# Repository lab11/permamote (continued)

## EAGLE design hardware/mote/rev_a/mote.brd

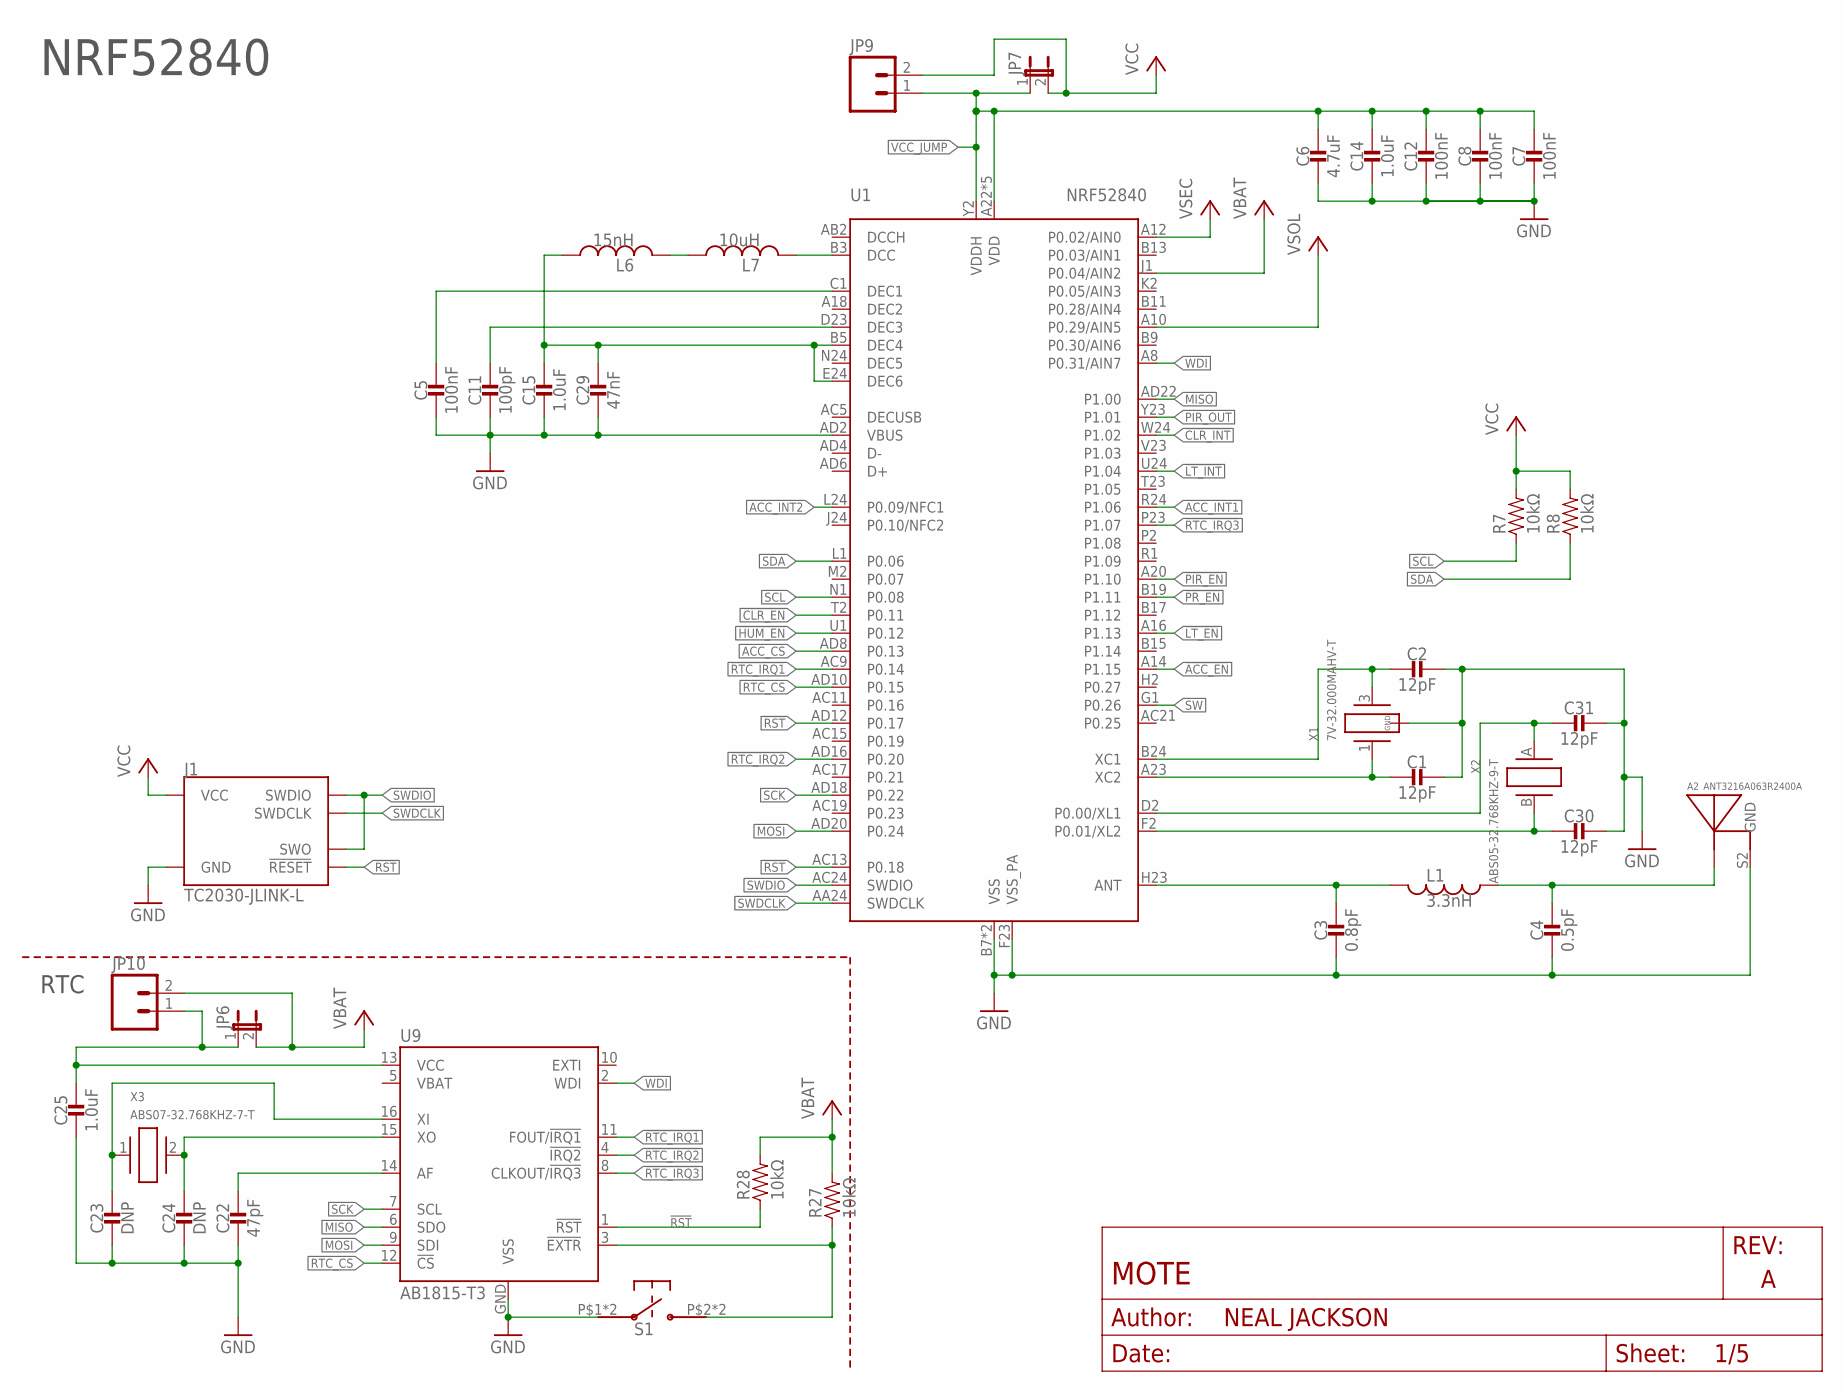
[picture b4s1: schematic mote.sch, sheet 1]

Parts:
A2: ANT3216A063R2400A
C1, C2, C30, C31: 12pF; 0402_CAP; DIGIKEY 490-6197-1-ND
C3: 0.8pF; 0402_CAP; DIGIKEY 490-6269-1-ND
C4: 0.5pF; 0402_CAP; DIGIKEY 490-6264-1-ND
C5, C7, C8, C12: 100nF; 0402_CAP; DIGIKEY 490-6328-1-ND
C6: 4.7uF; 0603_CAP; DIGIKEY 445-5947-1-ND
C11: 100pF; 0402_CAP; DIGIKEY 490-5922-1-ND
C14, C15, C25: 1.0uF; 0402_CAP; DIGIKEY 490-7195-1-ND
C22: 47pF; 0402_CAP; DIGIKEY 490-5942-1-ND
C23, C24: DNP; 0402_CAP
C29: 47nF; 0402_CAP; DIGIKEY 445-1264-1-ND
J1: TC2030-JLINK-L; TC2030-IDC
JP6, JP7: JUMPER-2SMD-NC; SJ_2S
JP9, JP10: M02PTH; 1X02
L1: 3.3nH; 0402_CAP; DIGIKEY 535-10426-1-ND
L6: 15nH; 0402_CAP; DIGIKEY 587-1521-1-ND
L7: 10uH; 0603_CAP; DIGIKEY 490-4025-1-ND
R7, R8, R27, R28: 10kΩ; 0402_RES; DIGIKEY 311-10KJRCT-ND
S1: EVQP2
U1: NRF52840; AQFN73
U9: AB1815-T3; QFN-16-3MM
X1: 7V-32.000MAHV-T; TXC-7V
X2: ABS05-32.768KHZ-9-T; ABS05
X3: ABS07-32.768KHZ-7-T; 2-SMD

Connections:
!ACC_EN: U1.A14 (P1.15); also elsewhere on the board
!CLR_EN: U1.T2 (P0.11); also elsewhere on the board
!CLR_INT: U1.W24 (P1.02); also elsewhere on the board
!HUM_EN: U1.U1 (P0.12); also elsewhere on the board
!LT_EN: U1.A16 (P1.13); also elsewhere on the board
!LT_INT: U1.U24 (P1.04); also elsewhere on the board
!PIR_EN: U1.A20 (P1.10); also elsewhere on the board
!PR_EN: U1.B19 (P1.11); also elsewhere on the board
!RST: J1.3 (!RESET), R28.1, U1.AC13 (P0.18), U1.AD12 (P0.17), U9.1 (!RST); also elsewhere on the board
!RTC_EXTR: R27.1, S1.P$2, S1.P$4, U9.3 (!EXTR)
!RTC_IRQ1: U1.AC9 (P0.14), U9.11 (FOUT/!IRQ1); also elsewhere on the board
!RTC_IRQ2: U1.AD16 (P0.20), U9.4 (!IRQ2); also elsewhere on the board
!RTC_IRQ3: U1.P23 (P1.07), U9.8 (CLKOUT/!IRQ3); also elsewhere on the board
ACC_CS: U1.AD8 (P0.13); also elsewhere on the board
ACC_INT1: U1.R24 (P1.06); also elsewhere on the board
ACC_INT2: U1.L24 (P0.09/NFC1); also elsewhere on the board
GND: A2.S2 (GND), C1.1, C2.1, C3.2, C4.2, C5.2, C6.2, C7.2, C8.2, C11.2, C12.2, C14.2, C15.2, C22.2, C23.2, C24.2, C25.2, C29.2, C30.1, C31.1, J1.5 (GND), S1.P$1, S1.P$3, U1.AD2 (VBUS), U1.B7 (VSS), U1.F23 (VSS_PA), U1.GND (VSS), U9.GND (VSS), X1.2 (GND), X1.4 (GND); also elsewhere on the board
MISO: U1.AD22 (P1.00), U9.6 (SDO); also elsewhere on the board
MOSI: U1.AD20 (P0.24), U9.9 (SDI); also elsewhere on the board
unnamed: C5.1, U1.C1 (DEC1)
unnamed: C15.1, C29.1, L6.1, U1.B5 (DEC4), U1.E24 (DEC6)
unnamed: C11.1, U1.D23 (DEC3)
unnamed: C3.1, L1.2, U1.H23 (ANT)
unnamed: A2.S1 (ANTENNA), C4.1, L1.1
unnamed: C2.2, U1.B24 (XC1), X1.3 (2)
unnamed: C1.2, U1.A23 (XC2), X1.1
unnamed: C22.1, U9.14 (AF)
unnamed: C23.1, U9.16 (XI), X3.1
unnamed: C24.1, U9.15 (XO), X3.2
unnamed: C25.1, JP6.1, JP10.1, U9.13 (VCC)
unnamed: L7.2, U1.B3 (DCC)
unnamed: L6.2, L7.1
PIR_OUT: U1.Y23 (P1.01); also elsewhere on the board
RTC_CS: U1.AD10 (P0.15), U9.12 (!CS); also elsewhere on the board
SCK: U1.AD18 (P0.22), U9.7 (SCL); also elsewhere on the board
SCL: R7.1, U1.N1 (P0.08); also elsewhere on the board
SDA: R8.1, U1.L1 (P0.06); also elsewhere on the board
SW: U1.G1 (P0.26); also elsewhere on the board
SWDCLK: J1.4 (SWDCLK), U1.AA24 (SWDCLK); also elsewhere on the board
SWDIO: J1.2 (SWDIO), J1.6 (SWO), U1.AC24 (SWDIO); also elsewhere on the board
VBAT: JP6.2, JP10.2, R27.2, R28.2, U1.J1 (P0.04/AIN2); also elsewhere on the board
VCC: J1.1 (VCC), JP7.2, JP9.2, R7.2, R8.2; also elsewhere on the board
VCC_JUMP: C6.1, C7.1, C8.1, C12.1, C14.1, JP7.1, JP9.1, U1.A22 (VDD), U1.AD14 (VDD), U1.AD23 (VDD), U1.B1 (VDD), U1.W1 (VDD), U1.Y2 (VDDH); also elsewhere on the board
VSEC: U1.A12 (P0.02/AIN0); also elsewhere on the board
VSOL: U1.A10 (P0.29/AIN5); also elsewhere on the board
WDI: U1.A8 (P0.31/AIN7), U9.2 (WDI); also elsewhere on the board
XL1: C31.2, U1.D2 (P0.00/XL1), X2.A (1)
XL2: C30.2, U1.F2 (P0.01/XL2), X2.B (2)

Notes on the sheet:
NRF52840
RTC

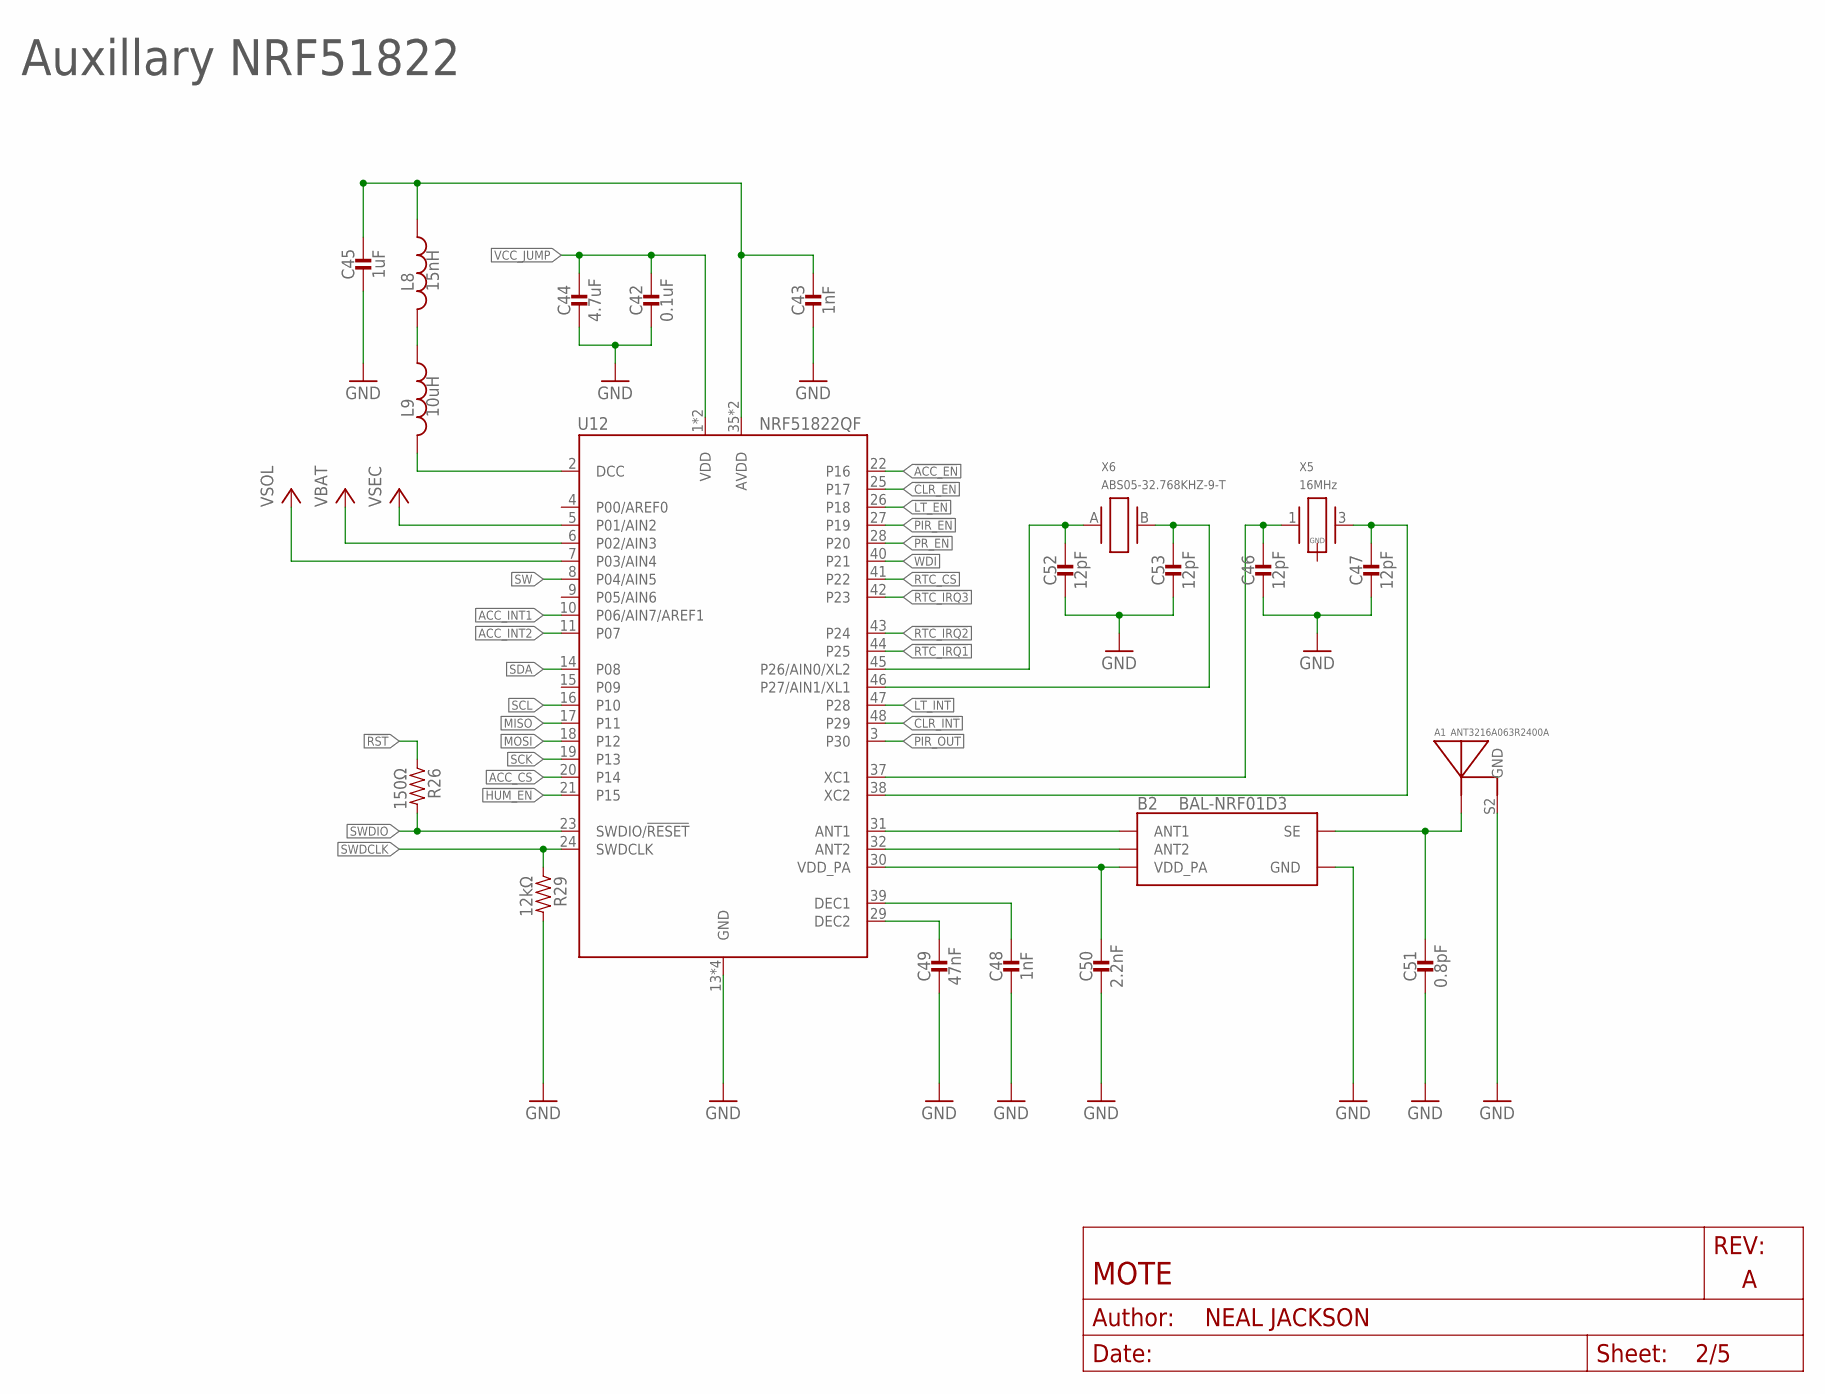
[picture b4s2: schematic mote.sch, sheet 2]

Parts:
A1: ANT3216A063R2400A
B2: BAL-NRF01D3
C42: 0.1uF; 0402_CAP; DIGIKEY 490-6328-1-ND
C43, C48: 1nF; 0402_CAP; DIGIKEY 490-1303-1-ND
C44: 4.7uF; 0402_CAP; DIGIKEY 445-5947-1-ND
C45: 1uF; 0402_CAP; DIGIKEY 1276-1513-1-ND
C46, C47, C52, C53: 12pF; 0402_CAP; DIGIKEY 490-6197-1-ND
C49: 47nF; 0402_CAP; DIGIKEY 445-1264-1-ND
C50: 2.2nF; 0402_CAP; DIGIKEY 490-5419-1-ND
C51: 0.8pF; 0402_CAP; DIGIKEY 490-6269-1-ND
L8: 15nH; 0402_CAP; DIGIKEY 587-1521-1-ND
L9: 10uH; 0603_CAP; DIGIKEY 490-4025-1-ND
R26: 150Ω; 0402_RES; DIGIKEY RHM12.0KCDCT-ND
R29: 12kΩ; 0402_RES; DIGIKEY RHM12.0KCDCT-ND
U12: NRF51822QF; QFN-48-6MM
X5: 16MHz; TXC-8Y; DIGIKEY 887-2003-1-ND
X6: ABS05-32.768KHZ-9-T; ABS05

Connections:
!ACC_EN: U12.22 (P16); also elsewhere on the board
!CLR_EN: U12.25 (P17); also elsewhere on the board
!CLR_INT: U12.48 (P29); also elsewhere on the board
!HUM_EN: U12.21 (P15); also elsewhere on the board
!LT_EN: U12.26 (P18); also elsewhere on the board
!LT_INT: U12.47 (P28); also elsewhere on the board
!PIR_EN: U12.27 (P19); also elsewhere on the board
!PR_EN: U12.28 (P20); also elsewhere on the board
!RST: R26.1; also elsewhere on the board
!RTC_IRQ1: U12.44 (P25); also elsewhere on the board
!RTC_IRQ2: U12.43 (P24); also elsewhere on the board
!RTC_IRQ3: U12.42 (P23); also elsewhere on the board
ACC_CS: U12.20 (P14); also elsewhere on the board
ACC_INT1: U12.10 (P06/AIN7/AREF1); also elsewhere on the board
ACC_INT2: U12.11 (P07); also elsewhere on the board
AVDD1: C43.1, C45.1, L8.1, U12.35 (AVDD), U12.36 (AVDD)
DCC1: L9.2, U12.2 (DCC)
GND: A1.S2 (GND), B2.GND, C42.2, C43.2, C44.2, C45.2, C46.2, C47.2, C48.2, C49.2, C50.2, C51.2, C52.2, C53.2, R29.2, U12.13 (GND), U12.33 (GND), U12.34 (GND), U12.GND; also elsewhere on the board
MISO: U12.17 (P11); also elsewhere on the board
MOSI: U12.18 (P12); also elsewhere on the board
unnamed: B2.ANT1, U12.31 (ANT1)
unnamed: B2.ANT2, U12.32 (ANT2)
unnamed: A1.S1 (ANTENNA), B2.SE, C51.1
unnamed: L8.2, L9.1
unnamed: C46.1, U12.37 (XC1), X5.1
unnamed: C47.1, U12.38 (XC2), X5.3 (2)
unnamed: C48.1, U12.39 (DEC1)
unnamed: C49.1, U12.29 (DEC2)
NRF_A2: C53.1, U12.46 (P27/AIN1/XL1), X6.B (2)
NRF_A3: C52.1, U12.45 (P26/AIN0/XL2), X6.A (1)
PIR_OUT: U12.3 (P30); also elsewhere on the board
RTC_CS: U12.41 (P22); also elsewhere on the board
SCK: U12.19 (P13); also elsewhere on the board
SCL: U12.16 (P10); also elsewhere on the board
SDA: U12.14 (P08); also elsewhere on the board
SW: U12.8 (P04/AIN5); also elsewhere on the board
SWDCLK: R29.1, U12.24 (SWDCLK); also elsewhere on the board
SWDIO: R26.2, U12.23 (SWDIO/!RESET); also elsewhere on the board
VBAT: U12.6 (P02/AIN3); also elsewhere on the board
VCC_JUMP: C42.1, C44.1, U12.1 (VDD), U12.12 (VDD); also elsewhere on the board
VDD_PA1: B2.VCC (VDD_PA), C50.1, U12.30 (VDD_PA)
VSEC: U12.5 (P01/AIN2); also elsewhere on the board
VSOL: U12.7 (P03/AIN4); also elsewhere on the board
WDI: U12.40 (P21); also elsewhere on the board

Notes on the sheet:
Auxillary NRF51822

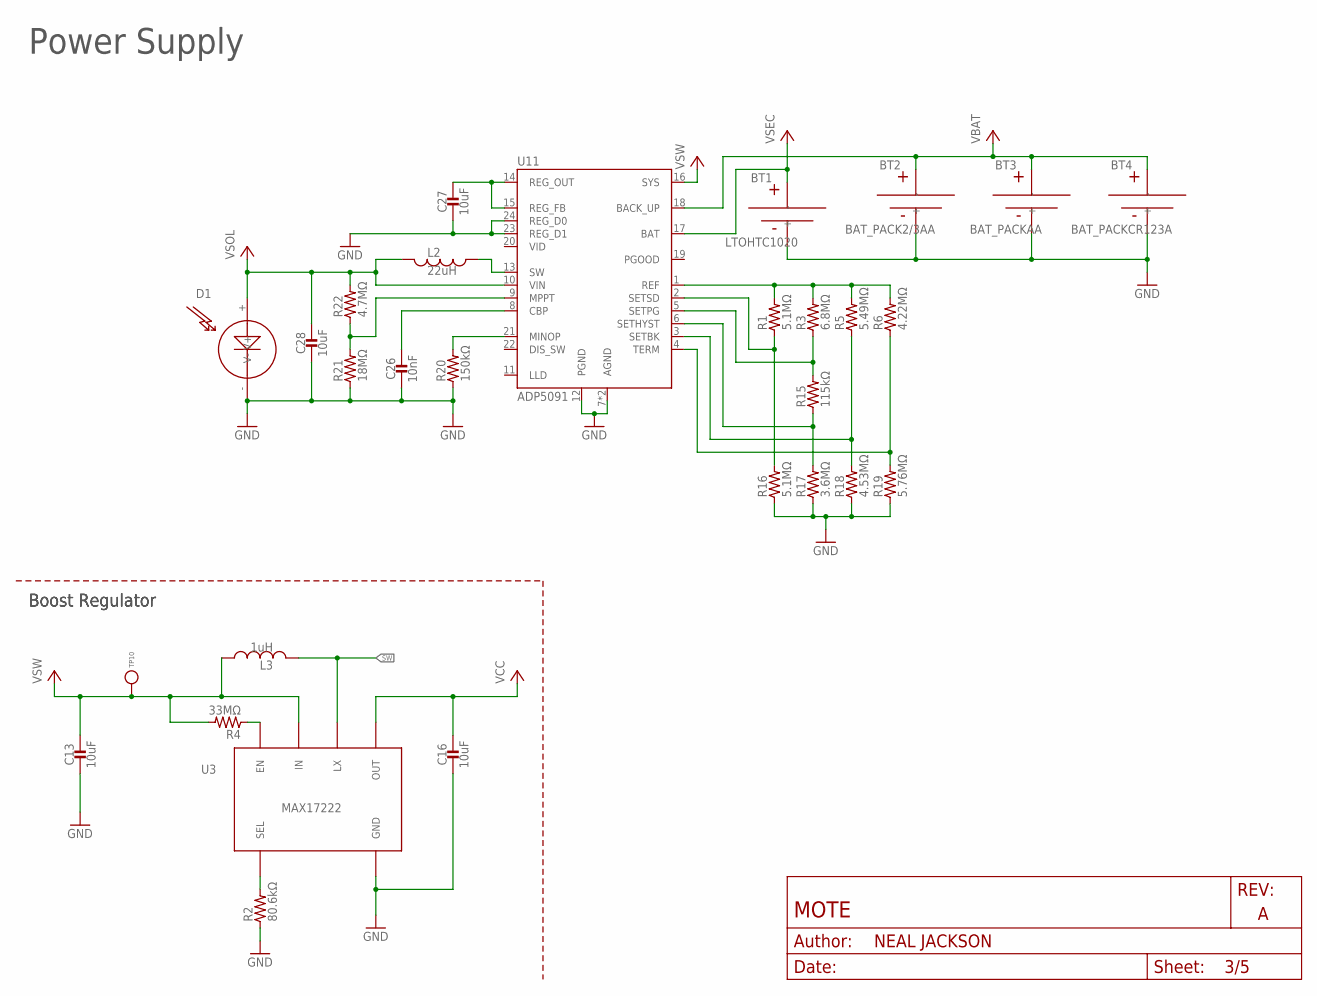
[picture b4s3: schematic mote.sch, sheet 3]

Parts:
BT1: LTOHTC1020; 1020
BT2: BAT_PACK2/3AA; 6S-2-3A
BT3: BAT_PACKAA; BHAA-3
BT4: BAT_PACKCR123A; BH123A
C13, C16, C27, C28: 10uF; 0603_CAP; DIGIKEY 490-3896-2-ND
C26: 10nF; 0603_CAP; DIGIKEY 490-4516-1-ND
D1: SOLARCELL; SOLAR_HOLES
L2: 22uH; 74437324220; DIGIKEY 732-3340-1-ND
L3: 1uH; IHL-2525CZ; DIGIKEY 541-2562-1-ND
R1, R16: 5.1MΩ; 0402_RES; DIGIKEY YAG3306CT-ND
R2: 80.6kΩ; 0603-RES; DIGIKEY 311-80.6KHRCT-ND
R3: 6.8MΩ; 0402_RES; DIGIKEY YAG3310CT-ND
R4: 33MΩ; 0603-RES; DIGIKEY HMC0603JT33M0CT-ND
R5: 5.49MΩ; 0603-RES; DIGIKEY 541-5.49MHCT-ND
R6: 4.22MΩ; 0402_RES; DIGIKEY 541-4.22MLCT-ND
R15: 115kΩ; 0402_RES; DIGIKEY YAG2956CT-ND
R17: 3.6MΩ; 0402_RES; DIGIKEY 311-3.60MLRCT-ND
R18: 4.53MΩ; 0402_RES; DIGIKEY 541-4.53MLCT-ND
R19: 5.76MΩ; 0805_RES; DIGIKEY 311-5.76MCRCT-ND
R20: 150kΩ; 0402_RES; DIGIKEY 311-1.00MLRCT-ND
R21: 18MΩ; 0603-RES; DIGIKEY P18MGCT-ND
R22: 4.7MΩ; 0402_RES; DIGIKEY YAG3304CT-ND
TP10: TEST_POINT_0.040IN; TESTPOINT_0.040IN
U3: MAX17222; UDFN-6-MAXIM
U11: ADP5091; QFN-24-4MM

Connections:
GND: BT1.-, BT2.-, BT3.-, BT4.-, C13.2, C16.2, C26.2, C27.2, C28.2, D1.- (V-), R2.1, R16.1, R17.1, R18.1, R19.1, R20.1, R21.1, U3.3 (GND), U11.7 (AGND), U11.12 (PGND), U11.23 (REG_D1), U11.24 (REG_D0), U11.GND_PAD (AGND); also elsewhere on the board
unnamed: R1.1, R16.2, U11.2 (SETSD)
unnamed: R1.2, R3.2, R5.2, R6.2, U11.1 (REF)
unnamed: R3.1, R15.2, U11.5 (SETPG)
unnamed: R2.2, U3.4 (SEL)
unnamed: R15.1, R17.2, U11.6 (SETHYST)
unnamed: R4.1, U3.6 (EN)
unnamed: R5.1, R18.2, U11.3 (SETBK)
unnamed: R6.1, R19.2, U11.4 (TERM)
unnamed: R20.2, U11.21 (MINOP)
unnamed: C26.1, U11.8 (CBP)
unnamed: R21.2, R22.1, U11.9 (MPPT)
unnamed: L2.P$1 (1), U11.13 (SW)
unnamed: C27.1, U11.14 (REG_OUT), U11.15 (REG_FB)
SW: L3.P$2 (2), U3.2 (LX); also elsewhere on the board
VBAT: BT2.+, BT3.+, BT4.+, U11.18 (BACK_UP); also elsewhere on the board
VCC: C16.1, U3.1 (OUT); also elsewhere on the board
VSEC: BT1.+, U11.17 (BAT); also elsewhere on the board
VSOL: C28.1, D1.+ (V+), L2.P$2 (2), R22.2, U11.10 (VIN); also elsewhere on the board
VSW: C13.1, L3.P$1 (1), R4.2, TP10.TESTPOINT, U3.5 (IN), U11.16 (SYS)

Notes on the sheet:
Power Supply
Boost Regulator

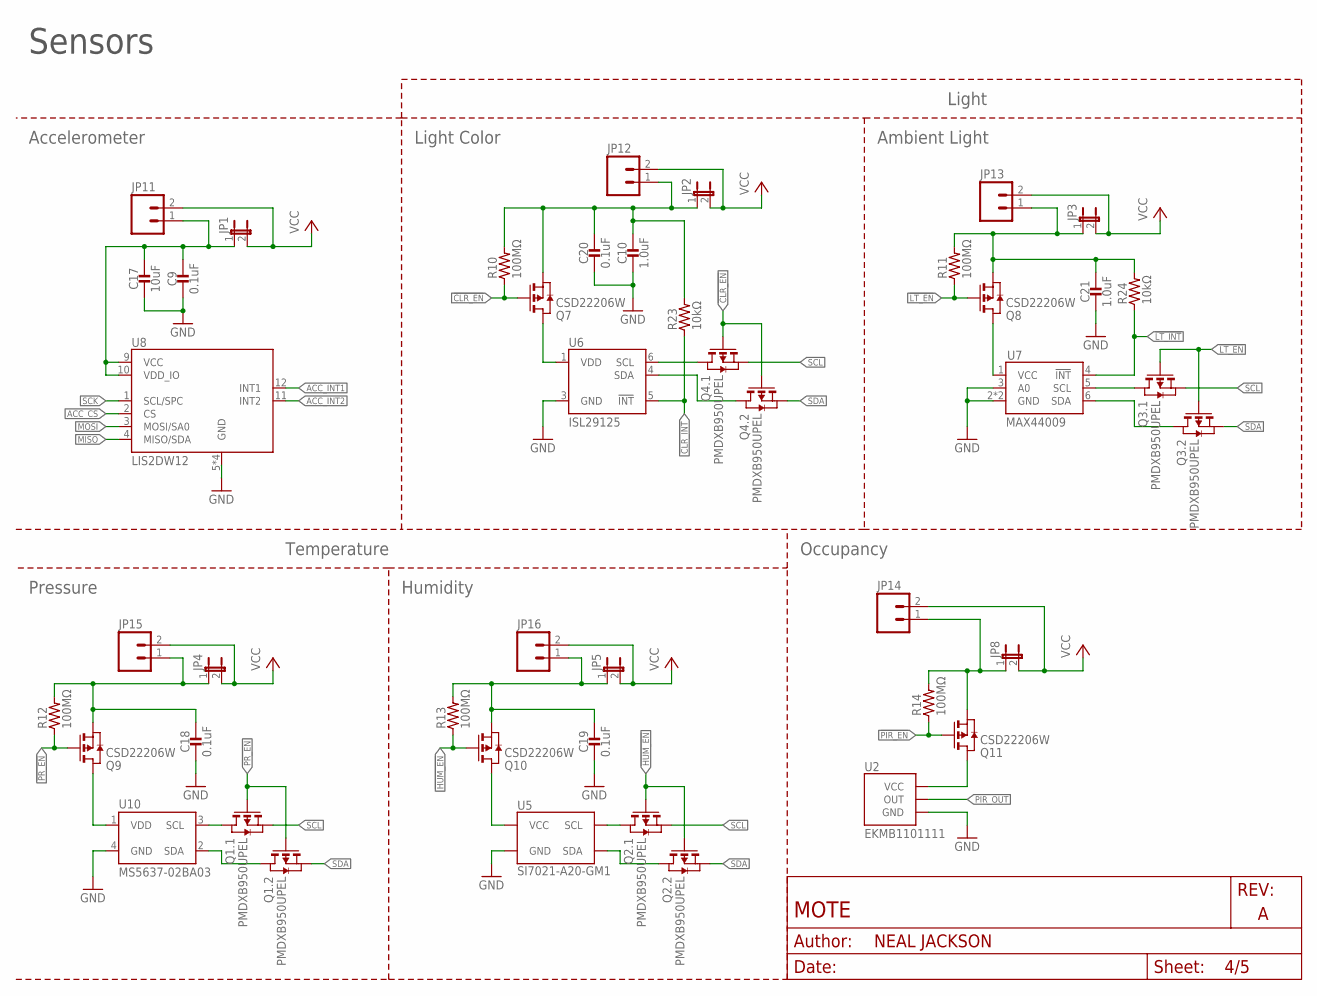
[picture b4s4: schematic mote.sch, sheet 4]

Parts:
C9, C18, C19, C20: 0.1uF; 0402_CAP; DIGIKEY 490-6328-1-ND
C10, C21: 1.0uF; 0402_CAP; DIGIKEY 490-7195-1-ND
C17: 10uF; 0603_CAP; DIGIKEY 490-3896-2-ND
JP1, JP2, JP3, JP4, JP5, JP8: JUMPER-2SMD-NC; SJ_2S
JP11, JP12, JP13, JP14, JP15, JP16: M02PTH; 1X02
Q1, Q2, Q3, Q4: PMDXB950UPEL; XDFN-6
Q7, Q8, Q9, Q10, Q11: CSD22206W; DSBGA
R10, R11, R12, R13, R14: 100MΩ; 0402_RES; DIGIKEY 541-100MAHCT-ND
R23, R24: 10kΩ; 0402_RES; DIGIKEY 311-10KJRCT-ND
U2: EKMB1101111; AMN2
U5: SI7021-A20-GM1; DFN-6/3MM
U6: ISL29125; ODFN-6-1.5MMX1.6MM
U7: MAX44009; UDFN-6-EXPOSED
U8: LIS2DW12; LGA-12
U10: MS5637-02BA03; 4-SMD

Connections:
!CLR_EN: Q4.2 (G), Q4.5 (G), Q7.A1 (G), R10.1; also elsewhere on the board
!CLR_INT: R23.1, U6.5 (!INT); also elsewhere on the board
!HUM_EN: Q2.2 (G), Q2.5 (G), Q10.A1 (G), R13.1; also elsewhere on the board
!LT_EN: Q3.2 (G), Q3.5 (G), Q8.A1 (G), R11.1; also elsewhere on the board
!LT_INT: R24.1, U7.4 (!INT); also elsewhere on the board
!PIR_EN: Q11.A1 (G), R14.1; also elsewhere on the board
!PR_EN: Q1.2 (G), Q1.5 (G), Q9.A1 (G), R12.1; also elsewhere on the board
ACC_CS: U8.2 (CS); also elsewhere on the board
ACC_INT1: U8.12 (INT1); also elsewhere on the board
ACC_INT2: U8.11 (INT2); also elsewhere on the board
GND: C9.2, C10.2, C17.2, C18.2, C19.2, C20.2, C21.2, U2.GND, U5.2 (GND), U6.3 (GND), U7.2 (GND), U7.3 (A0), U7.EP (GND), U8.5 (GND), U8.6 (GND), U8.7 (GND), U8.8 (GND), U10.4 (GND); also elsewhere on the board
MISO: U8.4 (MISO/SDA); also elsewhere on the board
MOSI: U8.3 (MOSI/SA0); also elsewhere on the board
unnamed: C9.1, C17.1, JP1.1, JP11.1, U8.9 (VCC), U8.10 (VDD_IO)
unnamed: C18.1, JP4.1, JP15.1, Q9.A2 (S), Q9.A3 (S), Q9.B1 (S), Q9.B2 (S), Q9.B3 (S), R12.2
unnamed: Q8.C1 (D), Q8.C2 (D), Q8.C3 (D), U7.1 (VCC)
unnamed: Q9.C1 (D), Q9.C2 (D), Q9.C3 (D), U10.1 (VDD)
unnamed: Q10.C1 (D), Q10.C2 (D), Q10.C3 (D), U5.5 (VCC)
unnamed: Q11.C1 (D), Q11.C2 (D), Q11.C3 (D), U2.VCC
unnamed: JP8.1, JP14.1, Q11.A2 (S), Q11.A3 (S), Q11.B1 (S), Q11.B2 (S), Q11.B3 (S), R14.2
unnamed: Q7.C1 (D), Q7.C2 (D), Q7.C3 (D), U6.1 (VDD)
unnamed: C10.1, C20.1, JP2.1, JP12.1, Q7.A2 (S), Q7.A3 (S), Q7.B1 (S), Q7.B2 (S), Q7.B3 (S), R10.2, R23.2
unnamed: Q1.6 (D), U10.3 (SCL)
unnamed: C19.1, JP5.1, JP16.1, Q10.A2 (S), Q10.A3 (S), Q10.B1 (S), Q10.B2 (S), Q10.B3 (S), R13.2
unnamed: C21.1, JP3.1, JP13.1, Q8.A2 (S), Q8.A3 (S), Q8.B1 (S), Q8.B2 (S), Q8.B3 (S), R11.2, R24.2
unnamed: Q1.3 (D), U10.2 (SDA)
unnamed: Q2.3 (D), U5.1 (SDA)
unnamed: Q2.6 (D), U5.6 (SCL)
unnamed: Q3.3 (D), U7.6 (SDA)
unnamed: Q3.6 (D), U7.5 (SCL)
unnamed: Q4.3 (D), U6.4 (SDA)
unnamed: Q4.6 (D), U6.6 (SCL)
PIR_OUT: U2.OUT; also elsewhere on the board
SCK: U8.1 (SCL/SPC); also elsewhere on the board
SCL: Q1.1 (S), Q2.1 (S), Q3.1 (S), Q4.1 (S); also elsewhere on the board
SDA: Q1.4 (S), Q2.4 (S), Q3.4 (S), Q4.4 (S); also elsewhere on the board
VCC: JP1.2, JP2.2, JP3.2, JP4.2, JP5.2, JP8.2, JP11.2, JP12.2, JP13.2, JP14.2, JP15.2, JP16.2; also elsewhere on the board

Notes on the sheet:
Sensors
Accelerometer
Temperature
Humidity
Pressure
Ambient Light
Light Color
Light
Occupancy

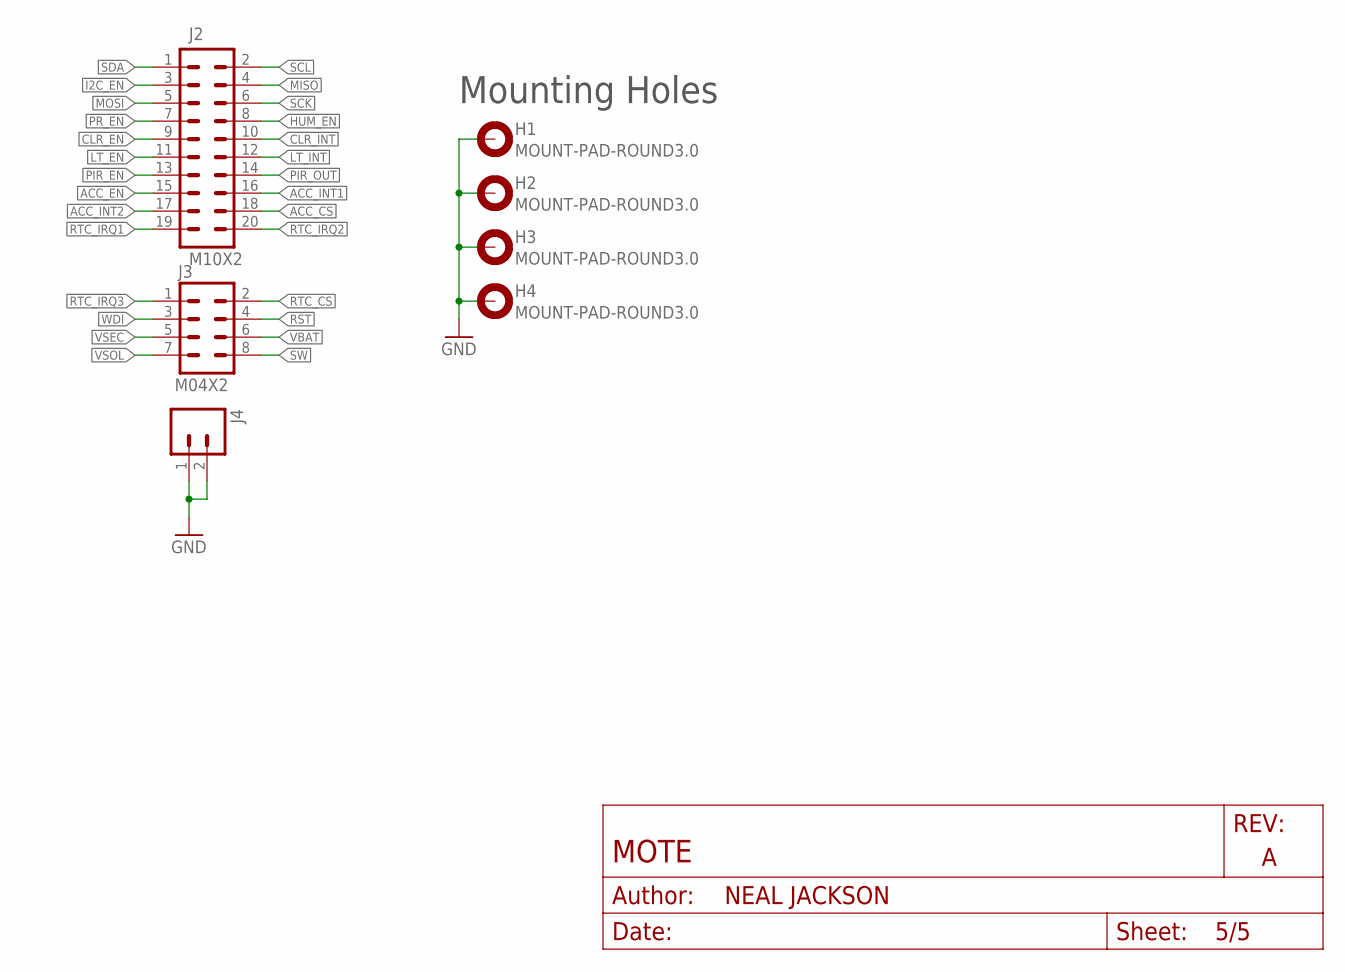
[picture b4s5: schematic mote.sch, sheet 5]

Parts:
H1, H2, H3, H4: MOUNT-PAD-ROUND3.0; 3,0-PAD
J2: M10X2; 2X10
J3: M04X2; 2X4
J4: M02PTH; 1X02

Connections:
!ACC_EN: J2.15; also elsewhere on the board
!CLR_EN: J2.9; also elsewhere on the board
!CLR_INT: J2.10; also elsewhere on the board
!HUM_EN: J2.8; also elsewhere on the board
!I2C_EN: J2.3
!LT_EN: J2.11; also elsewhere on the board
!LT_INT: J2.12; also elsewhere on the board
!PIR_EN: J2.13; also elsewhere on the board
!PR_EN: J2.7; also elsewhere on the board
!RST: J3.4; also elsewhere on the board
!RTC_IRQ1: J2.19; also elsewhere on the board
!RTC_IRQ2: J2.20; also elsewhere on the board
!RTC_IRQ3: J3.1; also elsewhere on the board
ACC_CS: J2.18; also elsewhere on the board
ACC_INT1: J2.16; also elsewhere on the board
ACC_INT2: J2.17; also elsewhere on the board
GND: H1.B3,0, H2.B3,0, H3.B3,0, H4.B3,0, J4.1, J4.2; also elsewhere on the board
MISO: J2.4; also elsewhere on the board
MOSI: J2.5; also elsewhere on the board
PIR_OUT: J2.14; also elsewhere on the board
RTC_CS: J3.2; also elsewhere on the board
SCK: J2.6; also elsewhere on the board
SCL: J2.2; also elsewhere on the board
SDA: J2.1; also elsewhere on the board
SW: J3.8; also elsewhere on the board
VBAT: J3.6; also elsewhere on the board
VSEC: J3.5; also elsewhere on the board
VSOL: J3.7; also elsewhere on the board
WDI: J3.3; also elsewhere on the board

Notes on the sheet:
Mounting Holes

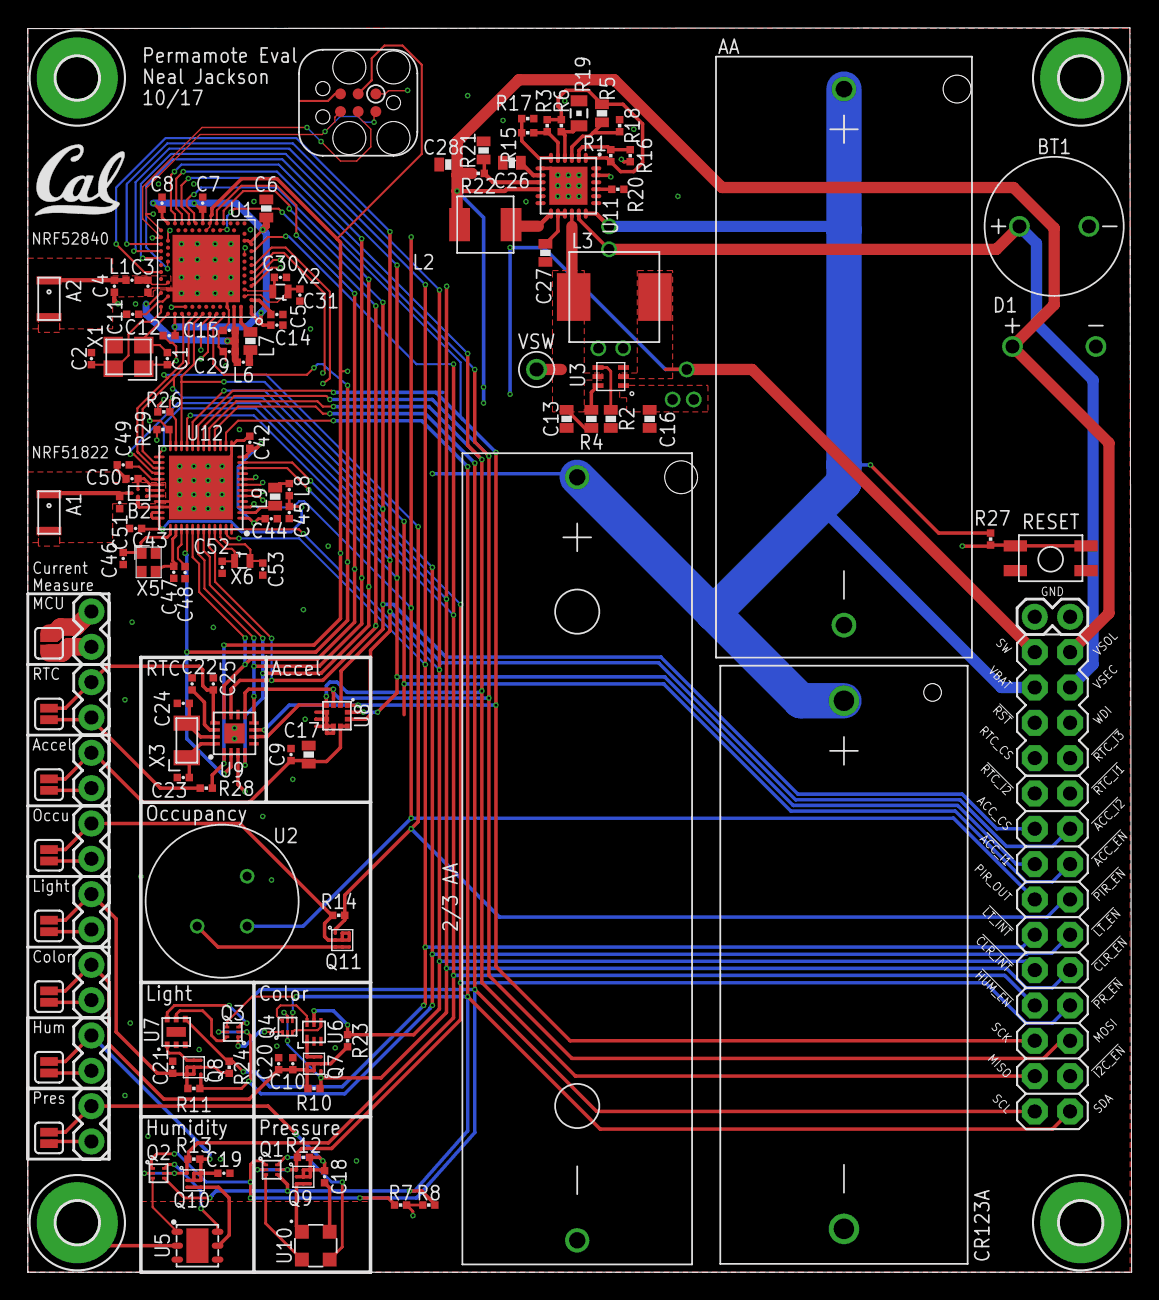
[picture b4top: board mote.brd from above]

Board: 4 copper layers, 79.4 x 89.5 mm, 137 parts (0 on the bottom side), 94 nets.

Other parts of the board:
U$1: UCB_CAL_200MIL

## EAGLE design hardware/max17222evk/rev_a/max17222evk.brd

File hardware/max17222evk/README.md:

MAX17222 Evaluation Kit/Breakout Board
======================================

This maxim chip is a new and more efficient low power boost converter 
(80% @ < 10ua, Iq = 350na). 

We wanted an evaluation kit but none are in stock so this breakout will
serve as our evaluation kit.

We specifically want to evaluate boost efficiency, and metrics that might
allow us to use the boost converter for an iCount energy metering system.

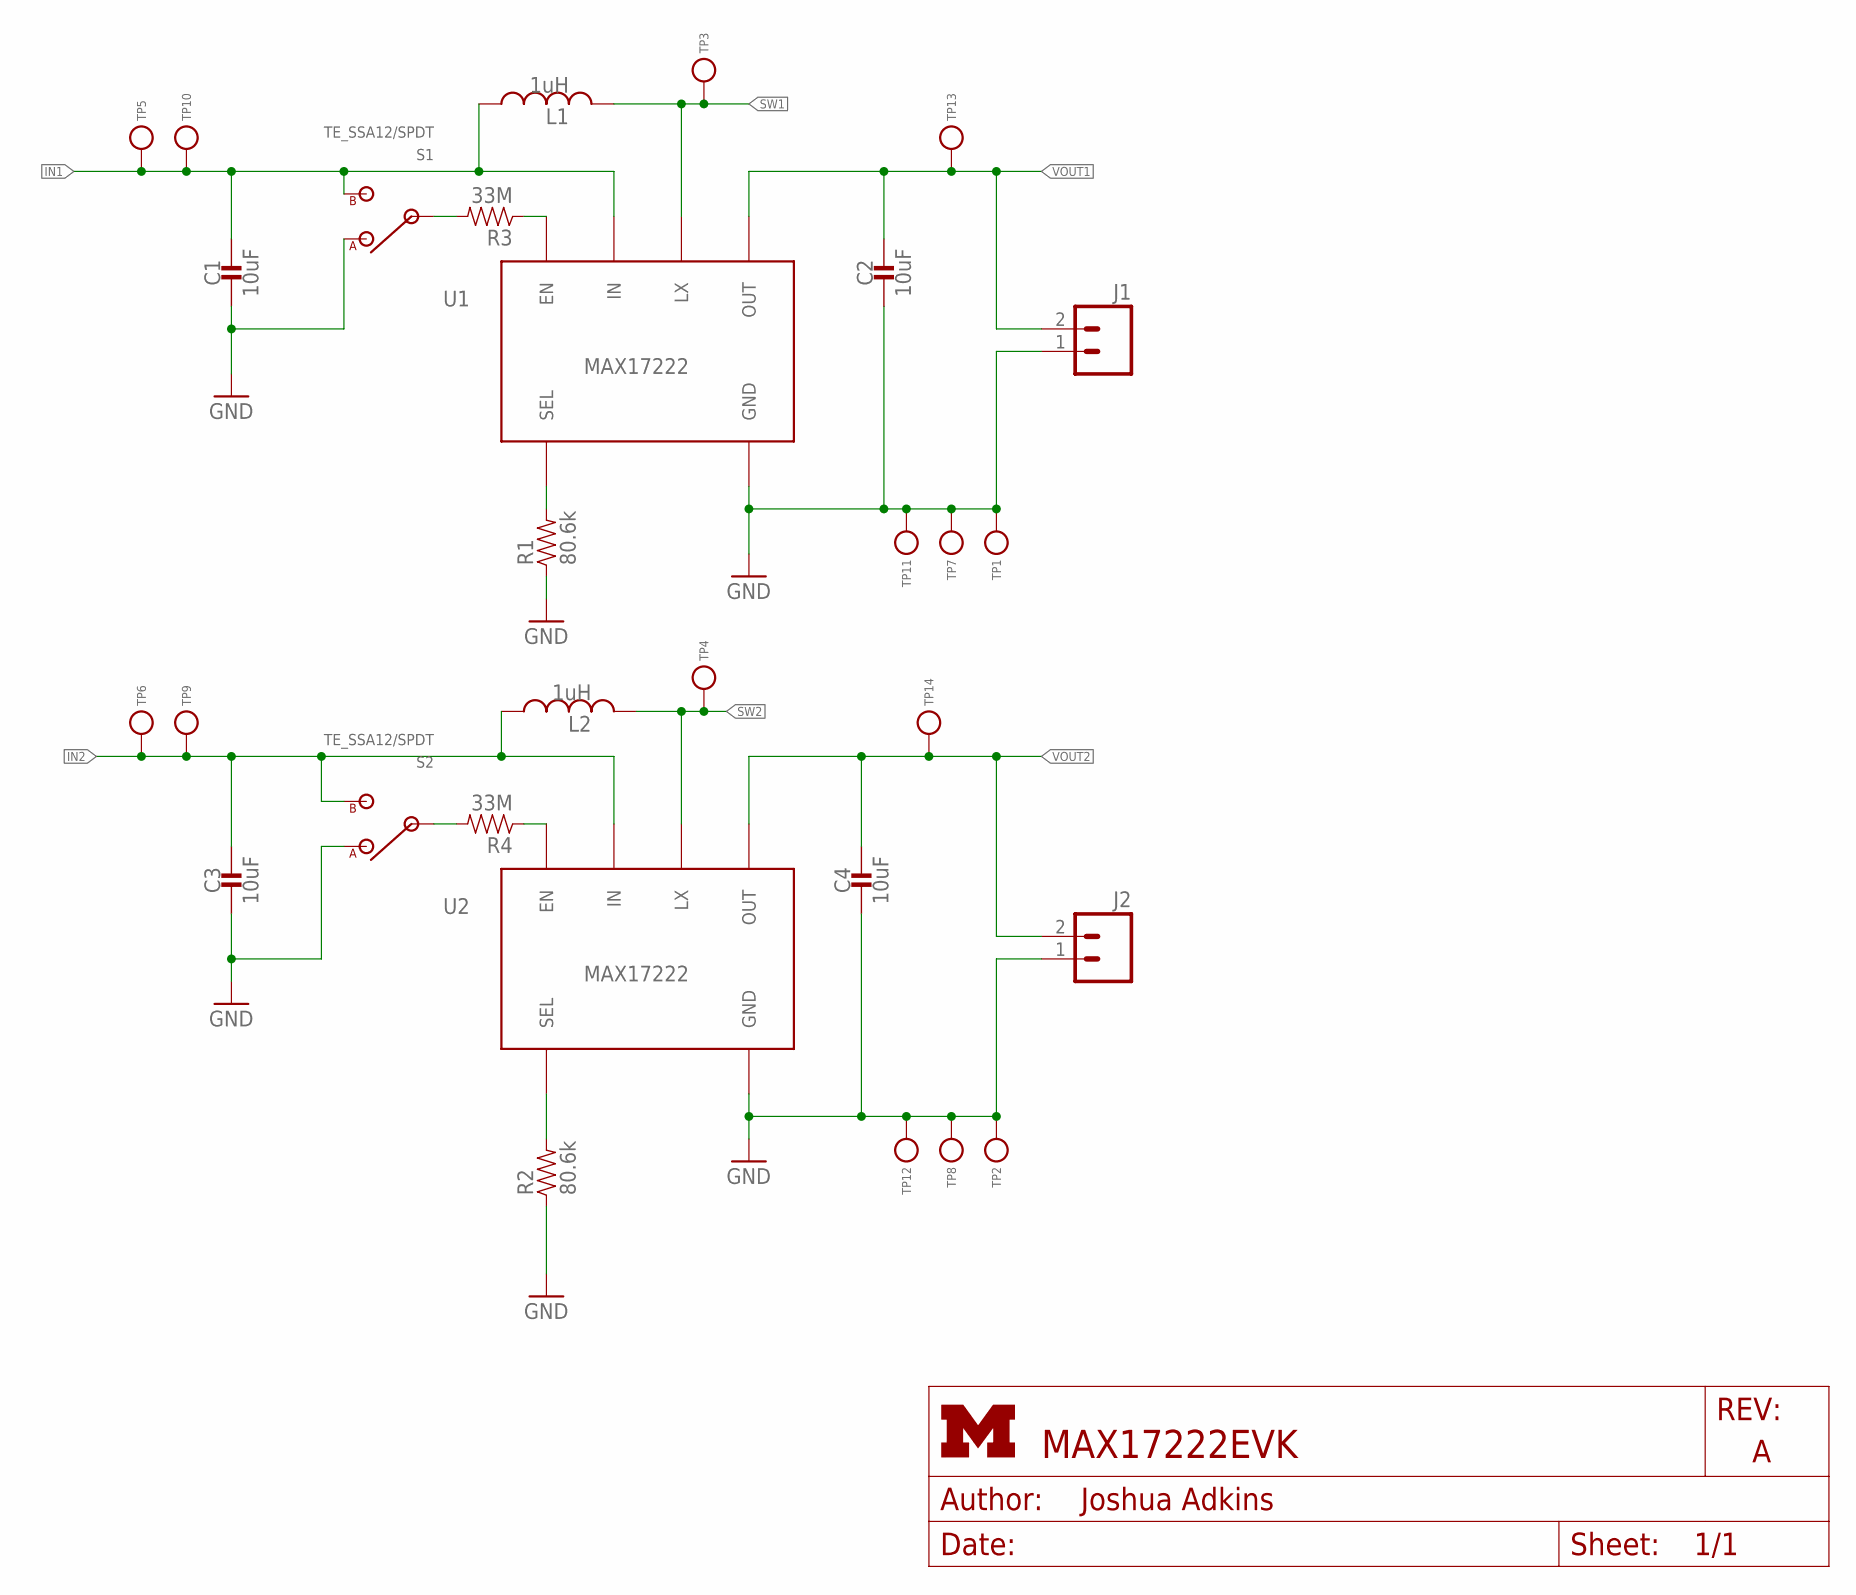
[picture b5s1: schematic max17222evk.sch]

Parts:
C1, C2, C3, C4: 10uF; 0603_CAP; DIGIKEY 490-3896-2-ND
J1, J2: M023.5MM; SCREWTERMINAL-3.5MM-2; DIGIKEY 277-1721-ND
L1: 1uH; IHL-2525CZ; DIGIKEY 541-2562-1-ND
L2: 1uH; DFE322512C; DIGIKEY 490-10590-1-ND
R1, R2: 80.6k; 0603-RES; DIGIKEY 311-80.6KHRCT-ND
R3, R4: 33M; 0603-RES; DIGIKEY HMC0603JT33M0CT-ND
S1, S2: TE_SSA12/SPDT
TP1, TP2, TP11, TP12: TEST_POINT_0.112IN; TESTPOINT_0.112IN; DIGIKEY 36-1519-2-ND
TP3, TP4, TP5, TP6, TP7, TP8, TP9, TP10, TP13, TP14: TEST_POINT_0.040IN; TESTPOINT_0.040IN
U1, U2: MAX17222; UDFN-6-MAXIM

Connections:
GND: C1.2, C2.2, C3.2, C4.2, J1.1, J2.1, R1.1, R2.1, S1.1 (A), S2.1 (A), TP1.1, TP2.1, TP7.TESTPOINT, TP8.TESTPOINT, TP11.1, TP12.1, U1.3 (GND), U2.3 (GND)
IN1: C1.1, L1.P$1 (1), S1.2 (B), TP5.TESTPOINT, TP10.TESTPOINT, U1.5 (IN)
IN2: C3.1, L2.P$1 (1), S2.2 (B), TP6.TESTPOINT, TP9.TESTPOINT, U2.5 (IN)
unnamed: R3.2, S1.IN
unnamed: R3.1, U1.6 (EN)
unnamed: R4.2, S2.IN
unnamed: R4.1, U2.6 (EN)
unnamed: R1.2, U1.4 (SEL)
unnamed: R2.2, U2.4 (SEL)
SW1: L1.P$2 (2), TP3.TESTPOINT, U1.2 (LX)
SW2: L2.P$2 (2), TP4.TESTPOINT, U2.2 (LX)
VOUT1: C2.1, J1.2, TP13.TESTPOINT, U1.1 (OUT)
VOUT2: C4.1, J2.2, TP14.TESTPOINT, U2.1 (OUT)
